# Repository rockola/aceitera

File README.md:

# aceitera

AMZ Mini Booster with mods

* v0.1: initial import, unverified

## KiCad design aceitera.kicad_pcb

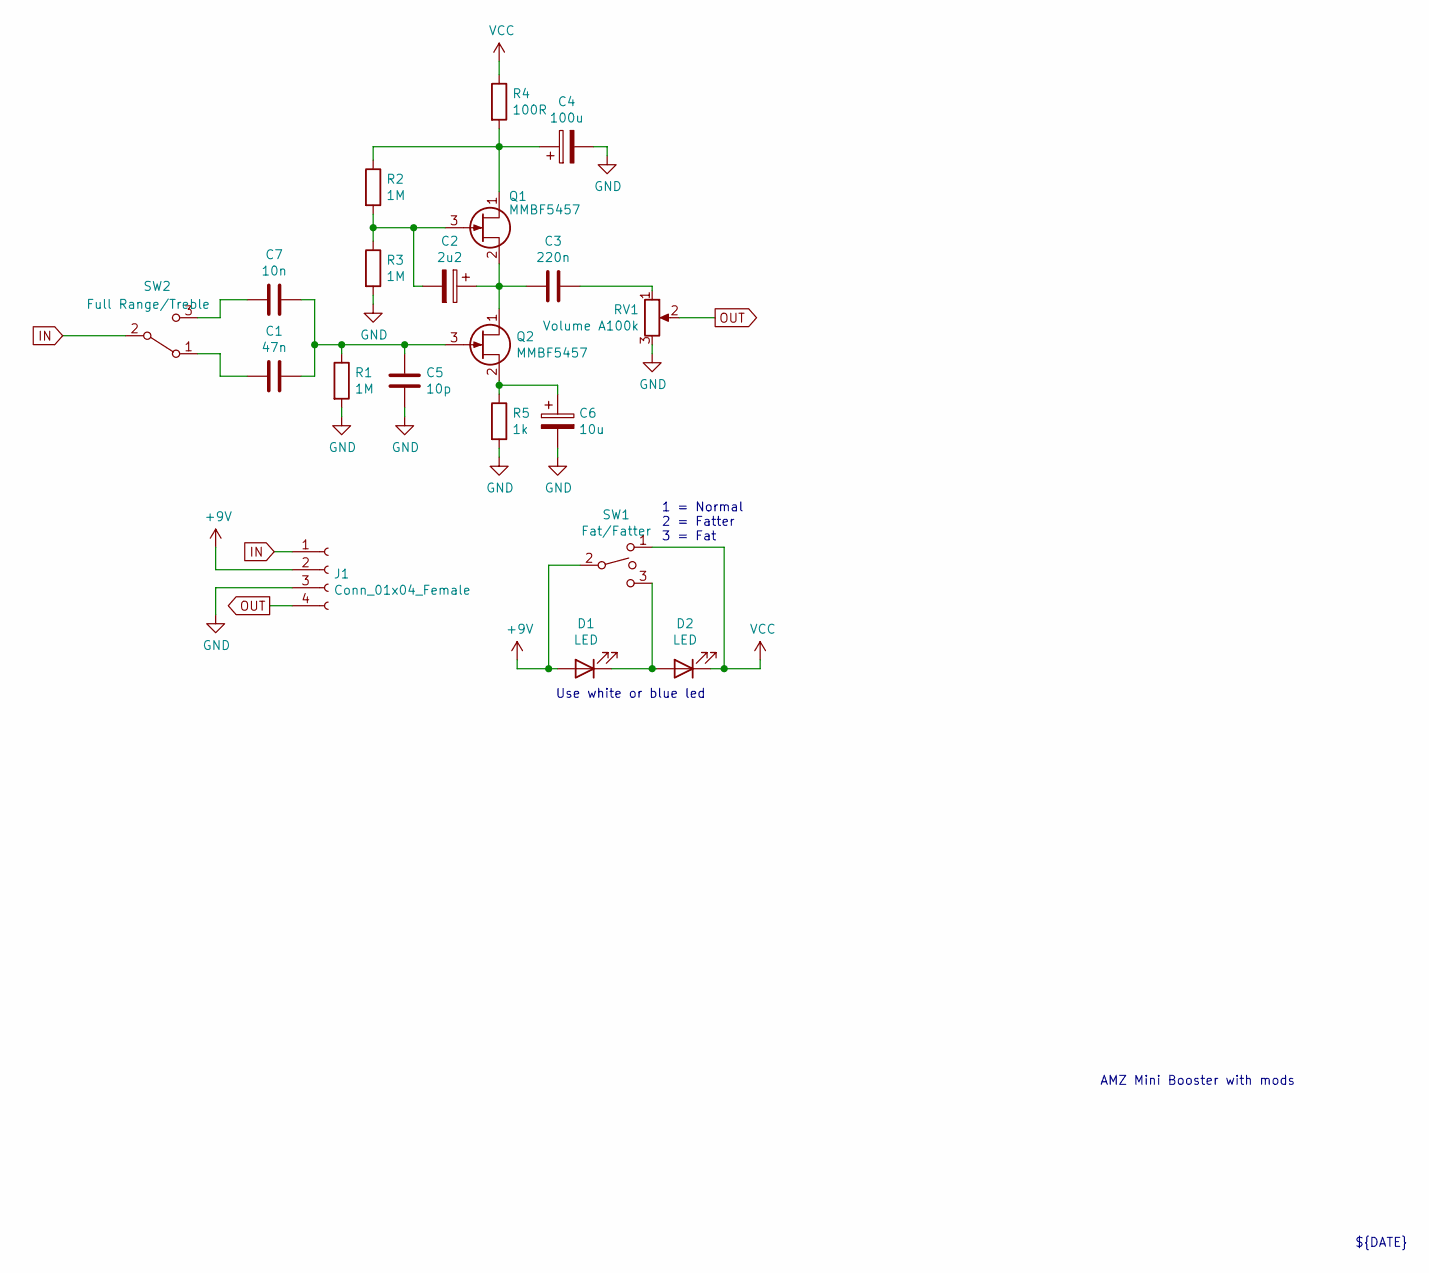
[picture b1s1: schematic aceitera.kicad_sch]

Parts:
C1: 47n; C_0805_2012Metric_Pad1.15x1.40mm_HandSolder
C2: 2u2; CP_D5.0_P2.50
C3: 220n; C_0805_2012Metric_Pad1.15x1.40mm_HandSolder
C4: 100u; CP_D5.0_P2.50
C5: 10p; C_0805_2012Metric_Pad1.15x1.40mm_HandSolder
C6: 10u; CP_D5.0_P2.50
C7: 10n; C_0805_2012Metric_Pad1.15x1.40mm_HandSolder
D1, D2: LED; LED.3mm
J1: Conn_01x04_Female; Stomp_IVGO_P2.00mm
Q1, Q2: MMBF5457; SOT-23_Handsoldering
R1, R2, R3: 1M; R_0805_2012Metric_Pad1.15x1.40mm_HandSolder
R4: 100R; R_0805_2012Metric_Pad1.15x1.40mm_HandSolder
R5: 1k; R_0805_2012Metric_Pad1.15x1.40mm_HandSolder
RV1: Volume A100k; Header_1x03_P2.00mm
SW1: Fat/Fatter; Header_1x03_P2.00mm
SW2: Full Range/Treble; Header_1x03_P2.00mm

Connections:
+9V: D1.2 (A), J1.2, SW1.2
GND: C4.2, C5.2, C6.2, J1.3, R1.2, R3.2, R5.2, RV1.3
IN: J1.1, SW2.2 (B)
unnamed: C1.1, SW2.1 (A)
unnamed: C1.2, C5.1, C7.2, Q2.3 (G), R1.1
unnamed: C2.1, C3.1, Q1.2 (S), Q2.1 (D)
unnamed: C2.2, Q1.3 (G), R2.2, R3.1
unnamed: C3.2, RV1.1
unnamed: C4.1, Q1.1 (D), R2.1, R4.2
unnamed: C6.1, Q2.2 (S), R5.1
unnamed: C7.1, SW2.3 (C)
unnamed: D1.1 (K), D2.2 (A), SW1.3
OUT: J1.4, RV1.2
VCC: D2.1 (K), R4.1, SW1.1

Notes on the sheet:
AMZ Mini Booster with mods
${TITLE}
${REVISION}
${DATE}
1 = Normal 2 = Fatter 3 = Fat
Use white or blue led

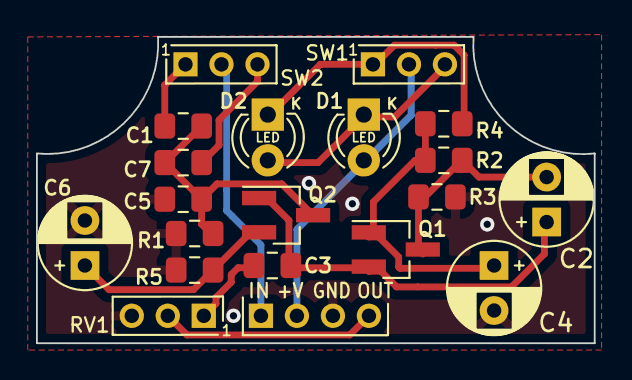
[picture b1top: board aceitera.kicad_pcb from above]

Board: 2 copper layers, 31.0 x 17.0 mm, 20 parts (0 on the bottom side), 14 nets.

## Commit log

2020-08-27 ignore kicad backups
2020-08-27 v0.1: initial version, Gerbers sent to Oshpark
2022-01-11 updated to KiCad 6.0
